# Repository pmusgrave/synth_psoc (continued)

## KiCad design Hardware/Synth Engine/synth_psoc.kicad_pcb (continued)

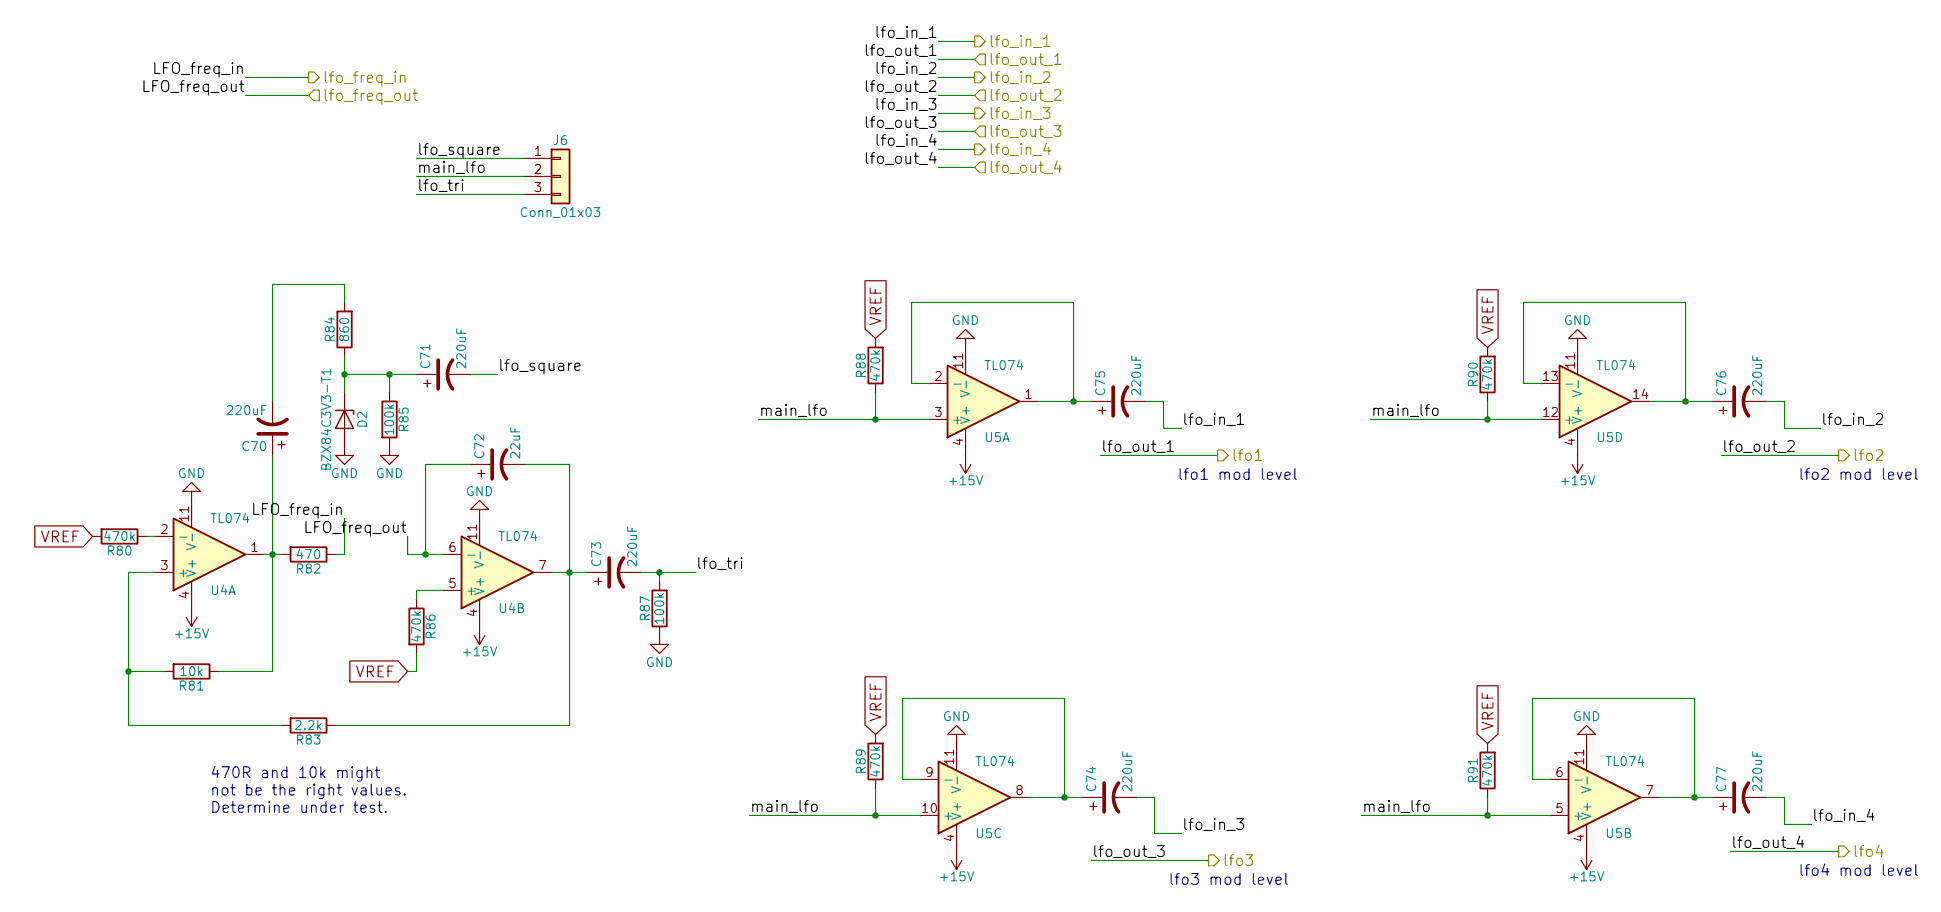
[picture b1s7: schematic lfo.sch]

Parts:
C70, C71, C73, C74, C75, C76, C77: 220uF; CP_Elec_8x10
C72: 22uF; CP_Elec_5x5.7
D2: BZX84C3V3-T1; SOT-23-3
J6: Conn_01x03; Pin_Header_Straight_1x03_Pitch2.54mm
R80, R86, R88, R89, R90, R91: 470k; 0805
R81: 10k; 0805
R82: 470; 0805
R83: 2.2k; 0805
R84: 860; 0805
R85, R87: 100k; 0805
U4, U5: TL074; SOIC-14_W3.9mm

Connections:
+15V: U4.4 (V+), U5.4 (V+); also elsewhere on the board
/LFO Modulation and Routing/lfo_square: C71.2, J6.1
/LFO Modulation and Routing/lfo_tri: C73.2, J6.3, R87.2
/LFO Modulation and Routing/main_lfo: J6.2, R88.1, R89.1, R90.1, R91.1, U5.3 (+), U5.5 (+), U5.10 (+), U5.12 (+)
/lfo_freq_in: R82.1; also elsewhere on the board
/lfo_freq_out: C72.1, U4.6 (-); also elsewhere on the board
/lfo_in_1: C75.2; also elsewhere on the board
/lfo_in_2: C76.2; also elsewhere on the board
/lfo_in_3: C74.2; also elsewhere on the board
/lfo_in_4: C77.2; also elsewhere on the board
GND: D2.2 (A), R85.2, R87.1, U4.11 (V-), U5.11 (V-); also elsewhere on the board
unnamed: C70.1, R81.1, R82.2, U4.1
unnamed: C70.2, R84.2
unnamed: C71.1, D2.1 (K), R84.1, R85.1
unnamed: C72.2, C73.1, R83.1, U4.7
unnamed: C74.1, U5.8, U5.9 (-)
unnamed: C75.1, U5.1, U5.2 (-)
unnamed: C76.1, U5.13 (-), U5.14
unnamed: C77.1, U5.6 (-), U5.7
unnamed: R80.1, U4.2 (-)
unnamed: R81.2, R83.2, U4.3 (+)
unnamed: R86.1, U4.5 (+)
VREF: R80.2, R86.2, R88.2, R89.2, R90.2, R91.2; also elsewhere on the board

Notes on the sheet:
470R and 10k might not be the right values. Determine under test.
lfo4 mod level
lfo2 mod level
lfo3 mod level
lfo1 mod level

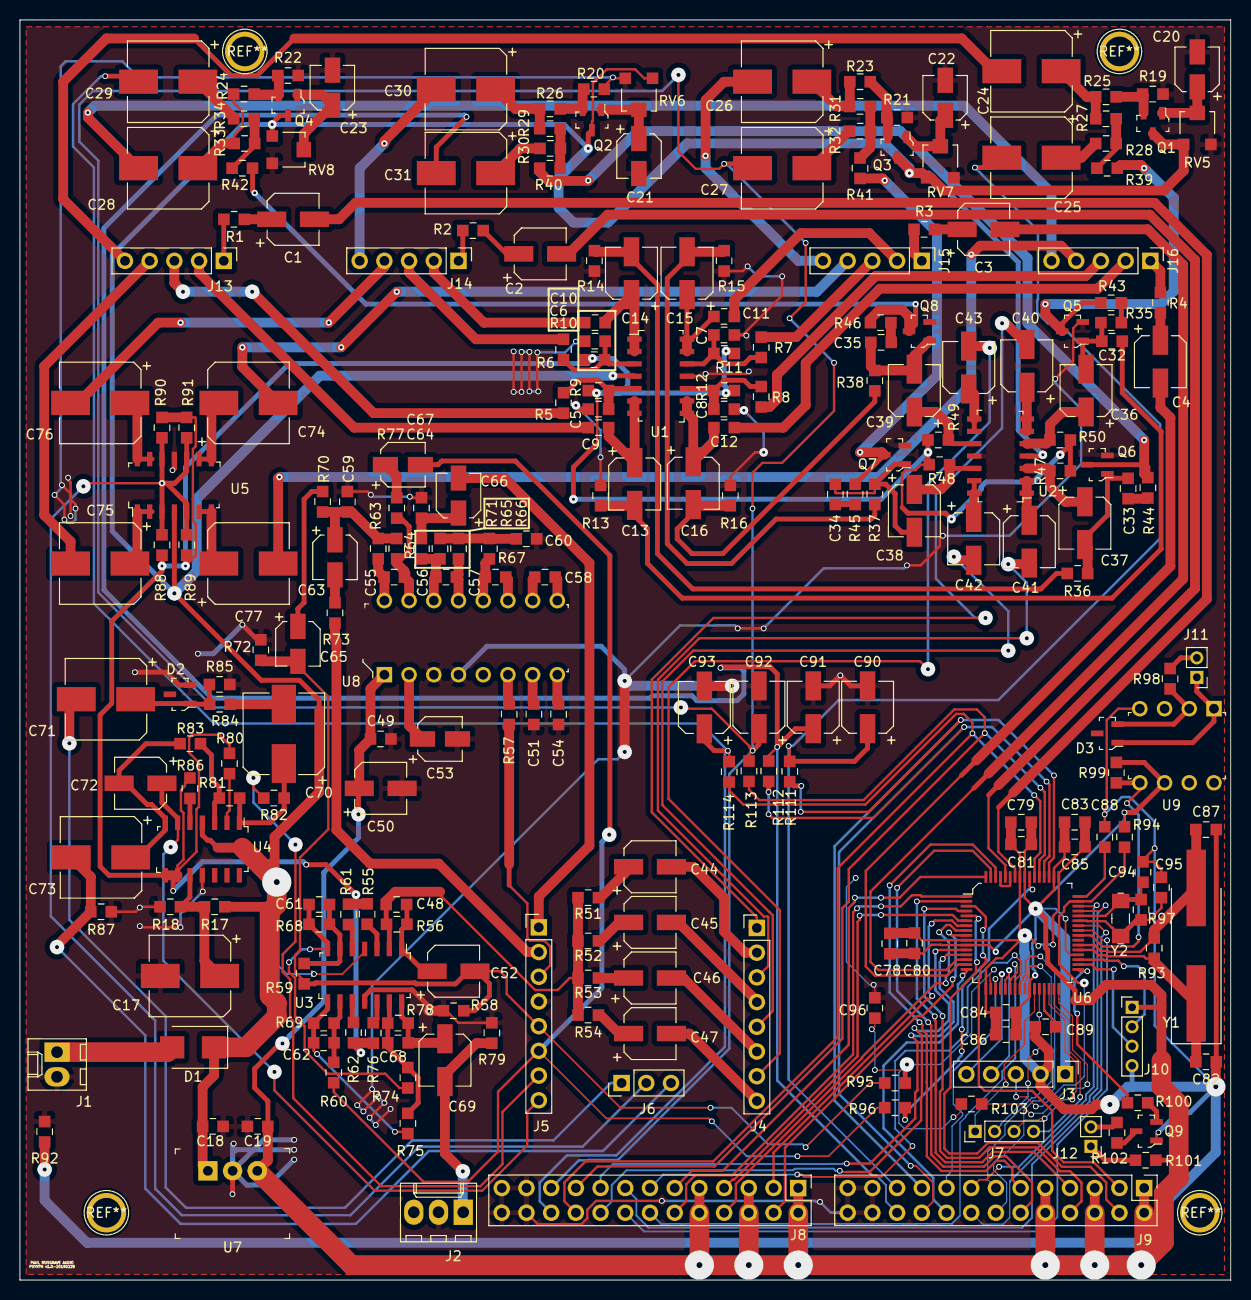
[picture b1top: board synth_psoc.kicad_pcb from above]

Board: 2 copper layers, 124.5 x 129.5 mm, 246 parts (0 on the bottom side), 211 nets.

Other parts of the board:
C96: 0.1uF; 0805
R103: 10k; 0805

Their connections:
/mcu_delay_in: C96.1, R103.1; also elsewhere on the board
GND: C96.2; also elsewhere on the board
unnamed 209: R103.2; also elsewhere on the board

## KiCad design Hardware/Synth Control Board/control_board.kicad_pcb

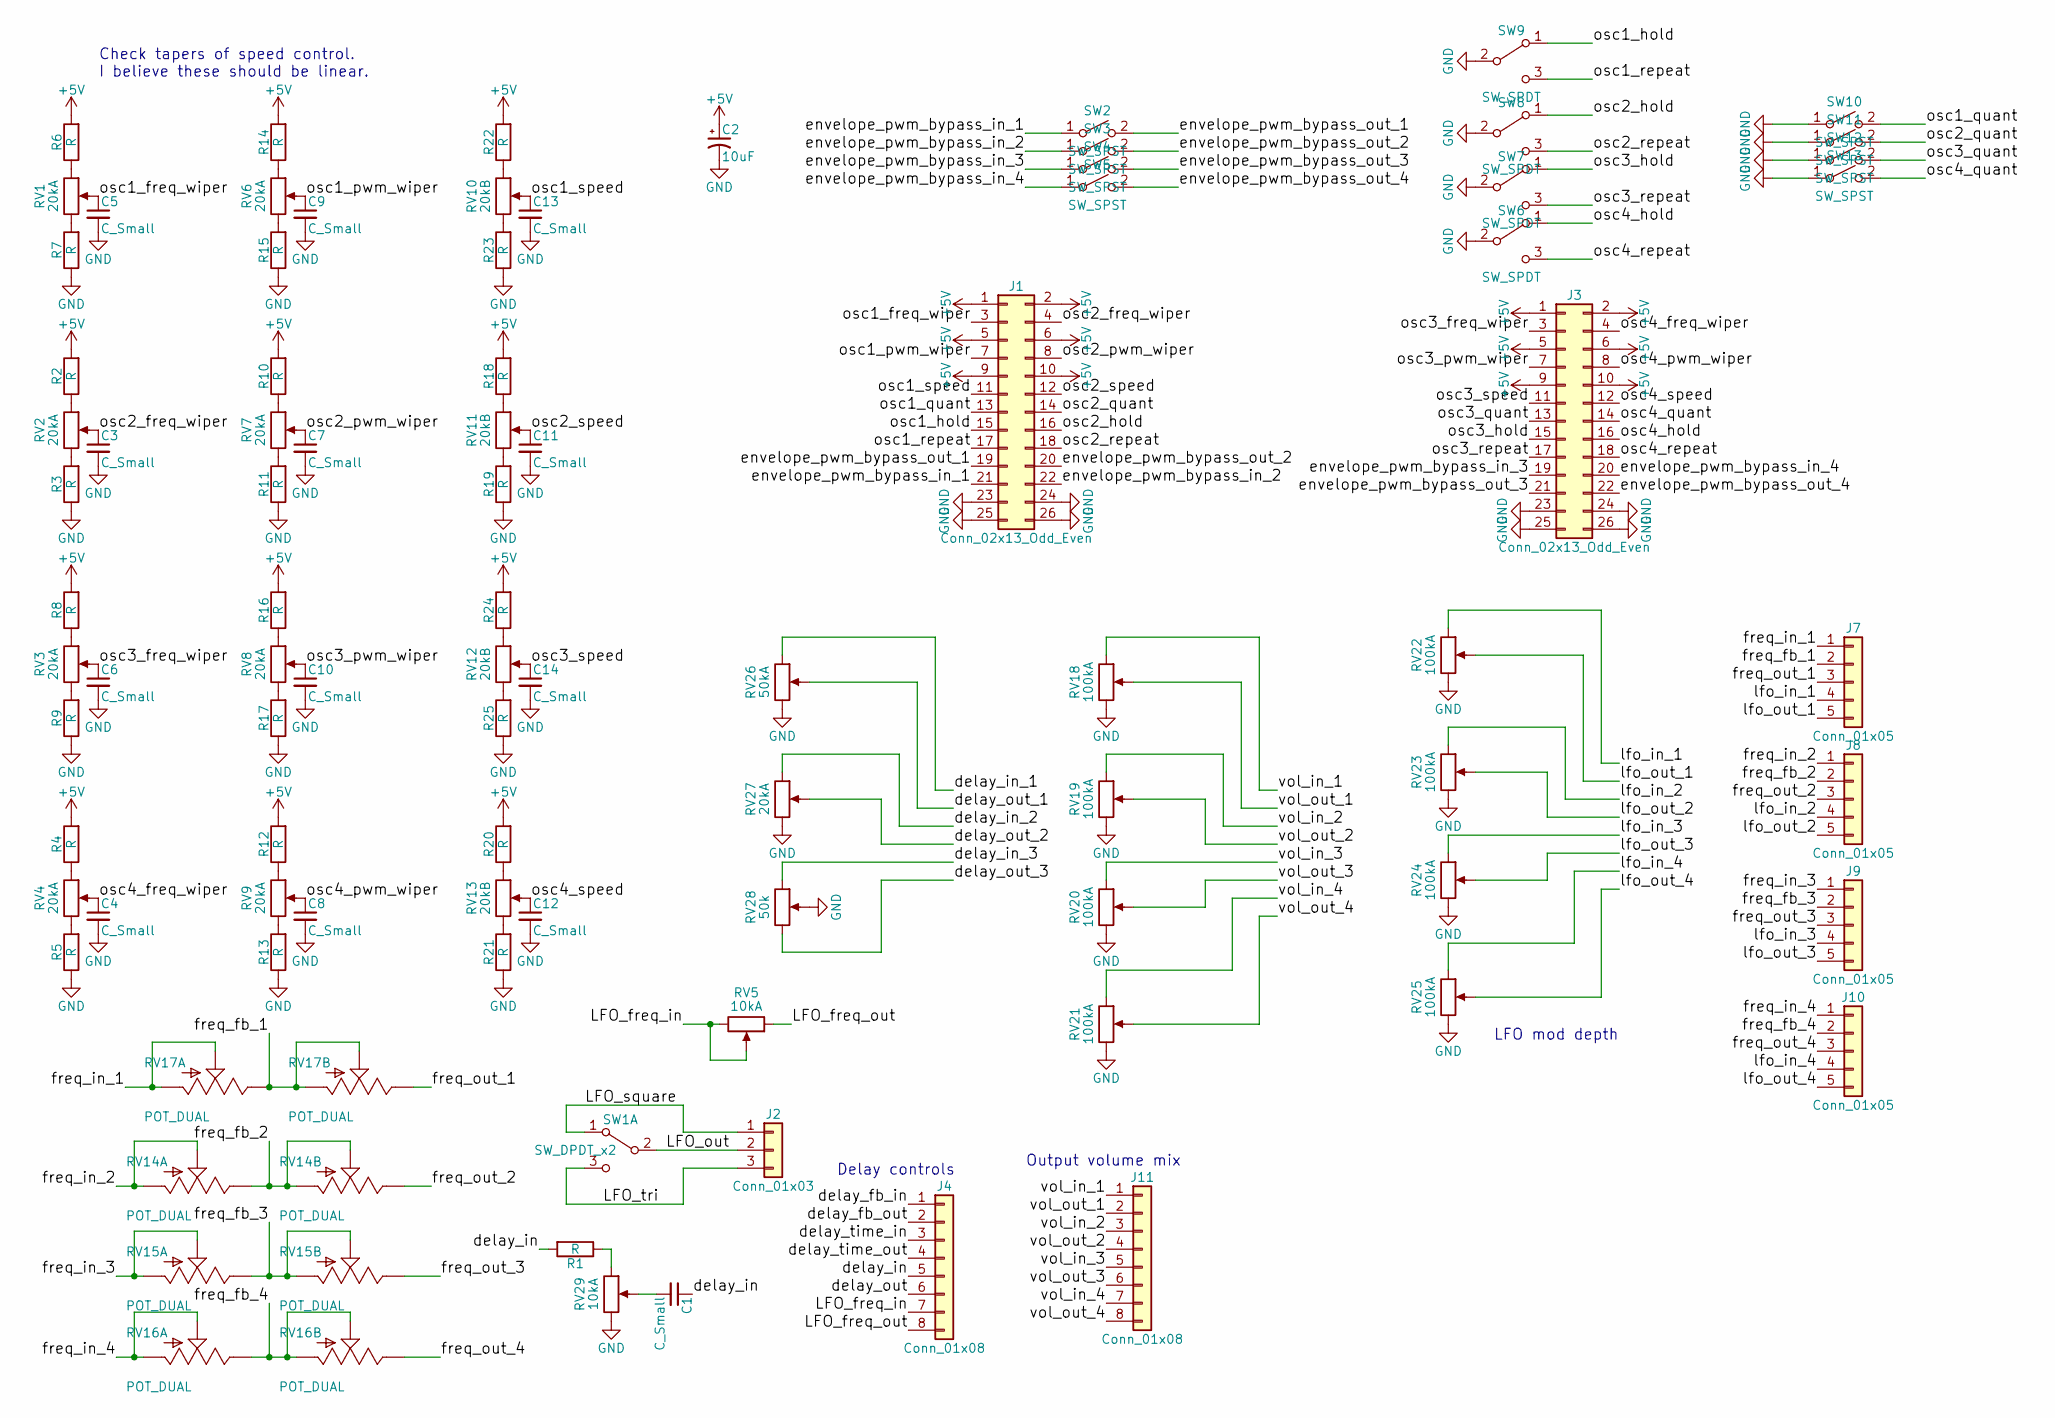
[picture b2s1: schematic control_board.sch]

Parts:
C1, C3, C4, C5, C6, C7, C8, C9, C10, C11, C12, C13, C14: C_Small; 0805
C2: 10uF; CP_Radial_D8.0mm_P5.00mm
J1, J3: Conn_02x13_Odd_Even; Pin_Header_Straight_2x13_Pitch2.54mm
J2: Conn_01x03; Pin_Header_Straight_1x03_Pitch2.54mm
J4, J11: Conn_01x08; Pin_Header_Straight_1x08_Pitch2.54mm
J7, J8, J9, J10: Conn_01x05; Pin_Header_Straight_1x05_Pitch2.54mm
R1, R2, R3, R4, R5, R6, R7, R8, R9, R10, R11, R12, R13, R14, R15, R16, R17, R18, R19, R20, R21, R22, R23, R24, R25: R; 0805
RV1, RV2, RV3, RV4, RV6, RV7, RV8, RV9, RV27: 20kA; Potentiometer_Bourns_PTV09A-1_Horizontal
RV5, RV29: 10kA; Potentiometer_Bourns_PTV09A-1_Horizontal
RV10, RV11, RV12, RV13: 20kB; Potentiometer_Bourns_PTV09A-1_Horizontal
RV14, RV15, RV16, RV17: POT_DUAL; POT_PANASONIC_DUAL_VERT_KIT
RV18, RV19, RV20, RV21, RV22, RV23, RV24, RV25: 100kA; Potentiometer_Bourns_PTV09A-1_Horizontal
RV26: 50kA; Potentiometer_Bourns_PTV09A-1_Horizontal
RV28: 50k; Potentiometer_Bourns_PTV09A-1_Horizontal
SW1: SW_DPDT_x2; switch_toggle_4.7mm_pitch
SW2, SW3, SW4, SW5, SW10, SW11, SW12, SW13: SW_SPST; switch_toggle_4.7mm_pitch
SW6, SW7, SW8, SW9: SW_SPDT; switch_toggle_4.7mm_pitch

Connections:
+5V: C2.1, J1.1, J1.2, J1.5, J1.6, J1.9, J1.10, J3.1, J3.2, J3.5, J3.6, J3.9, J3.10, R2.2, R4.2, R6.2, R8.2, R10.2, R12.2, R14.2, R16.2, R18.2, R20.2, R22.2, R24.2
/LFO_freq_in: J4.7, RV5.2, RV5.3
/LFO_freq_out: J4.8, RV5.1
/LFO_out: J2.2, SW1.2 (B)
/LFO_square: J2.1, SW1.1 (A)
/LFO_tri: J2.3, SW1.3 (C)
/delay_fb_in: J4.1
/delay_fb_out: J4.2
/delay_in: C1.1, J4.5, R1.2
/delay_in_1: RV26.1
/delay_in_2: RV27.1
/delay_in_3: RV28.1
/delay_out: J4.6
/delay_out_1: RV26.2
/delay_out_2: RV27.2
/delay_out_3: RV28.3
/delay_time_in: J4.3
/delay_time_out: J4.4
/envelope_pwm_bypass_in_1: J1.21, SW2.1 (A)
/envelope_pwm_bypass_in_2: J1.22, SW3.1 (A)
/envelope_pwm_bypass_in_3: J3.19, SW4.1 (A)
/envelope_pwm_bypass_in_4: J3.20, SW5.1 (A)
/envelope_pwm_bypass_out_1: J1.19, SW2.2 (B)
/envelope_pwm_bypass_out_2: J1.20, SW3.2 (B)
/envelope_pwm_bypass_out_3: J3.21, SW4.2 (B)
/envelope_pwm_bypass_out_4: J3.22, SW5.2 (B)
/freq_fb_1: J7.2, RV17.A1 (E), RV17.B2 (S), RV17.B3 (A)
/freq_fb_2: J8.2, RV14.A1 (E), RV14.B2 (S), RV14.B3 (A)
/freq_fb_3: J9.2, RV15.A1 (E), RV15.B2 (S), RV15.B3 (A)
/freq_fb_4: J10.2, RV16.A1 (E), RV16.B2 (S), RV16.B3 (A)
/freq_in_1: J7.1, RV17.A2 (S), RV17.A3 (A)
/freq_in_2: J8.1, RV14.A2 (S), RV14.A3 (A)
/freq_in_3: J9.1, RV15.A2 (S), RV15.A3 (A)
/freq_in_4: J10.1, RV16.A2 (S), RV16.A3 (A)
/freq_out_1: J7.3, RV17.B1 (E)
/freq_out_2: J8.3, RV14.B1 (E)
/freq_out_3: J9.3, RV15.B1 (E)
/freq_out_4: J10.3, RV16.B1 (E)
/lfo_in_1: J7.4, RV22.1
/lfo_in_2: J8.4, RV23.1
/lfo_in_3: J9.4, RV24.1
/lfo_in_4: J10.4, RV25.1
/lfo_out_1: J7.5, RV22.2
/lfo_out_2: J8.5, RV23.2
/lfo_out_3: J9.5, RV24.2
/lfo_out_4: J10.5, RV25.2
/osc1_freq_wiper: C5.1, J1.3, RV1.2
/osc1_hold: J1.15, SW9.1 (A)
/osc1_pwm_wiper: C9.1, J1.7, RV6.2
/osc1_quant: J1.13, SW10.2 (B)
/osc1_repeat: J1.17, SW9.3 (C)
/osc1_speed: C13.1, J1.11, RV10.2
/osc2_freq_wiper: C3.1, J1.4, RV2.2
/osc2_hold: J1.16, SW8.1 (A)
/osc2_pwm_wiper: C7.1, J1.8, RV7.2
/osc2_quant: J1.14, SW11.2 (B)
/osc2_repeat: J1.18, SW8.3 (C)
/osc2_speed: C11.1, J1.12, RV11.2
/osc3_freq_wiper: C6.1, J3.3, RV3.2
/osc3_hold: J3.15, SW7.1 (A)
/osc3_pwm_wiper: C10.1, J3.7, RV8.2
/osc3_quant: J3.13, SW12.2 (B)
/osc3_repeat: J3.17, SW7.3 (C)
/osc3_speed: C14.1, J3.11, RV12.2
/osc4_freq_wiper: C4.1, J3.4, RV4.2
/osc4_hold: J3.16, SW6.1 (A)
/osc4_pwm_wiper: C8.1, J3.8, RV9.2
/osc4_quant: J3.14, SW13.2 (B)
/osc4_repeat: J3.18, SW6.3 (C)
/osc4_speed: C12.1, J3.12, RV13.2
/vol_in_1: J11.1, RV18.1
/vol_in_2: J11.3, RV19.1
/vol_in_3: J11.5, RV20.1
/vol_in_4: J11.7, RV21.1
/vol_out_1: J11.2, RV18.2
/vol_out_2: J11.4, RV19.2
/vol_out_3: J11.6, RV20.2
/vol_out_4: J11.8, RV21.2
GND: C2.2, C3.2, C4.2, C5.2, C6.2, C7.2, C8.2, C9.2, C10.2, C11.2, C12.2, C13.2, C14.2, J1.23, J1.24, J1.25, J1.26, J3.23, J3.24, J3.25, J3.26, R3.1, R5.1, R7.1, R9.1, R11.1, R13.1, R15.1, R17.1, R19.1, R21.1, R23.1, R25.1, RV18.3, RV19.3, RV20.3, RV21.3, RV22.3, RV23.3, RV24.3, RV25.3, RV26.3, RV27.3, RV28.2, RV29.3, SW6.2 (B), SW7.2 (B), SW8.2 (B), SW9.2 (B), SW10.1 (A), SW11.1 (A), SW12.1 (A), SW13.1 (A)
unnamed: C1.2, RV29.2
unnamed: R1.1, RV29.1
unnamed: R2.1, RV2.1
unnamed: R3.2, RV2.3
unnamed: R4.1, RV4.1
unnamed: R5.2, RV4.3
unnamed: R6.1, RV1.1
unnamed: R7.2, RV1.3
unnamed: R8.1, RV3.1
unnamed: R9.2, RV3.3
unnamed: R10.1, RV7.1
unnamed: R11.2, RV7.3
unnamed: R12.1, RV9.1
unnamed: R13.2, RV9.3
unnamed: R14.1, RV6.1
unnamed: R15.2, RV6.3
unnamed: R16.1, RV8.1
unnamed: R17.2, RV8.3
unnamed: R18.1, RV11.1
unnamed: R19.2, RV11.3
unnamed: R20.1, RV13.1
unnamed: R21.2, RV13.3
unnamed: R22.1, RV10.1
unnamed: R23.2, RV10.3
unnamed: R24.1, RV12.1
unnamed: R25.2, RV12.3

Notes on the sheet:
Check tapers of speed control. I believe these should be linear.
Output volume mix
LFO mod depth
Delay controls

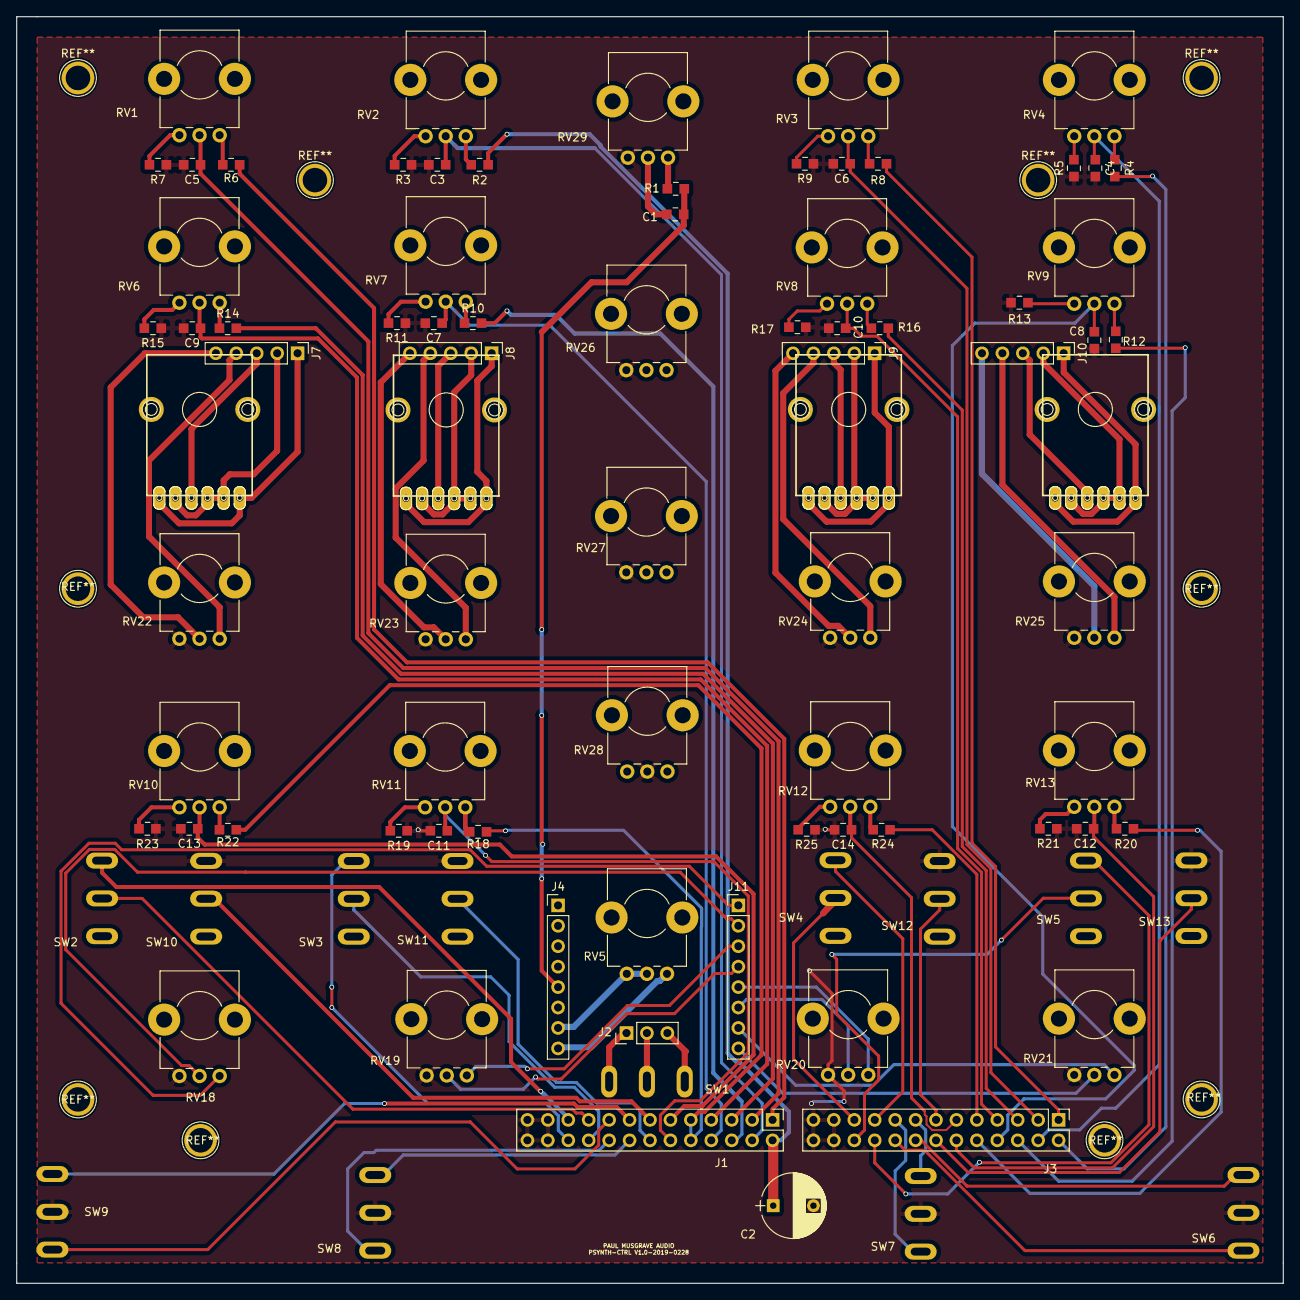
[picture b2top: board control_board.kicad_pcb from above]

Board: 2 copper layers, 157.5 x 157.5 mm, 90 parts (0 on the bottom side), 94 nets.

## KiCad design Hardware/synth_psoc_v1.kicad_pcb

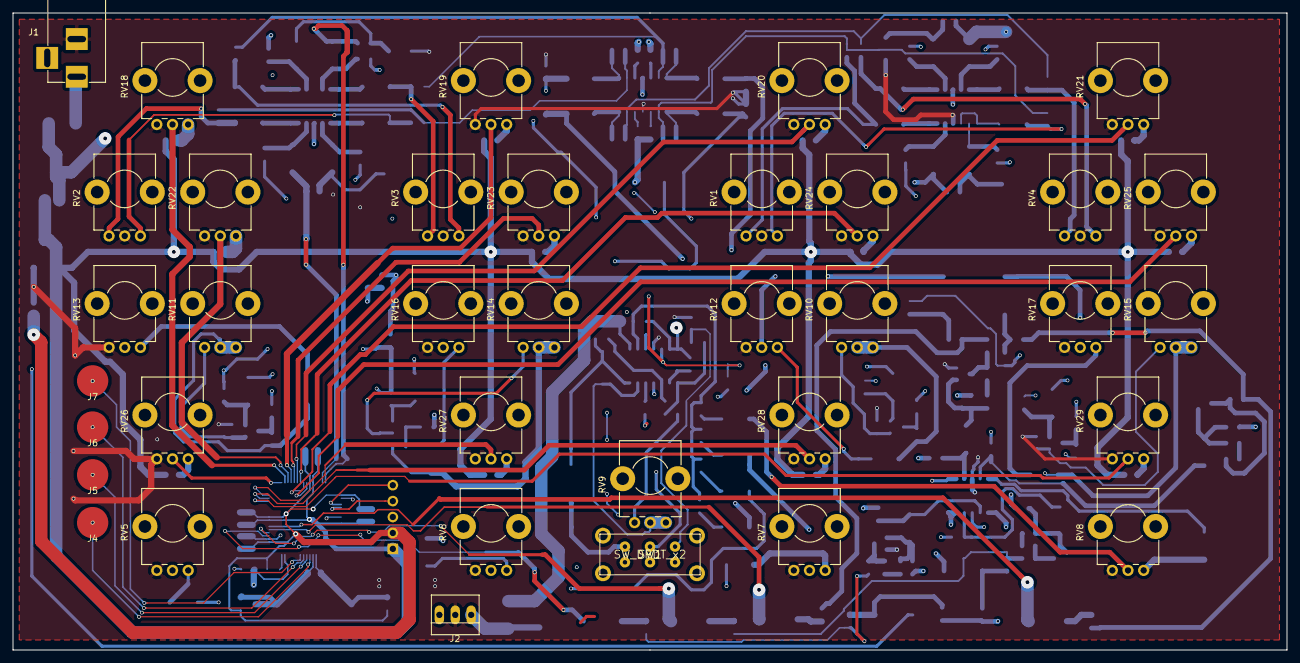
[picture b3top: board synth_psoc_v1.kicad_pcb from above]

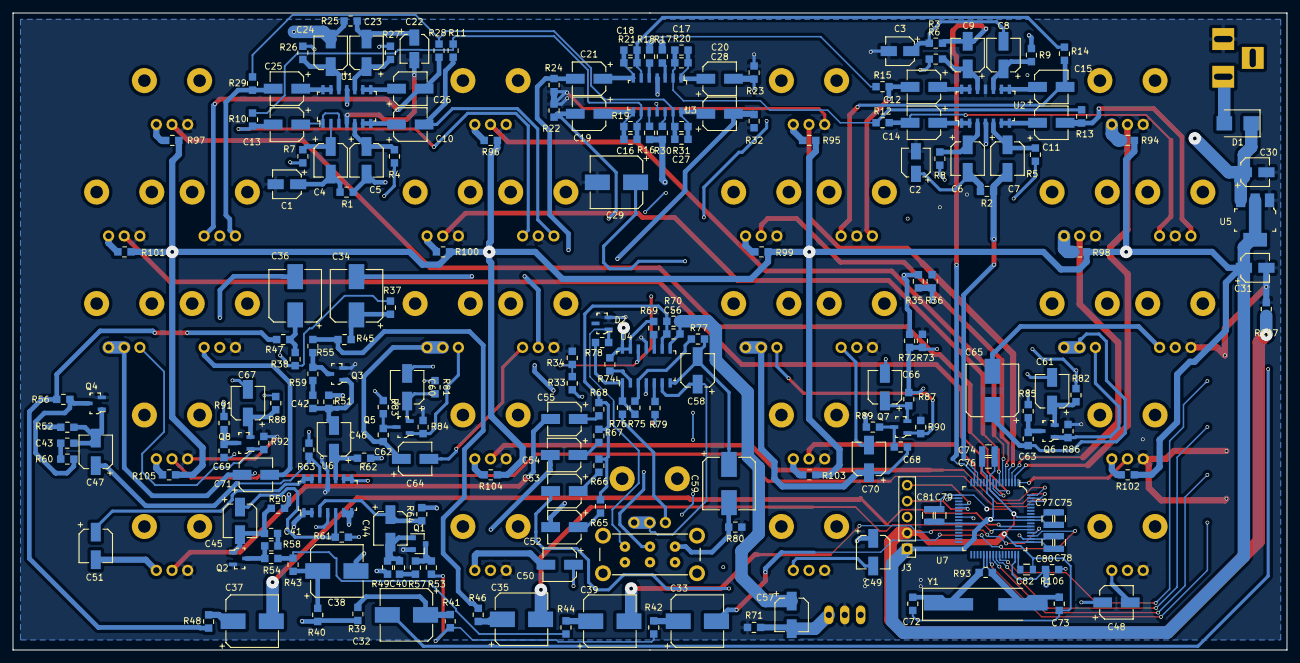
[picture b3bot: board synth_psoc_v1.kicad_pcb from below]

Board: 4 copper layers, 203.2 x 101.6 mm, 244 parts (208 on the bottom side), 177 nets.

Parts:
C1, C2, C3, C22, C30: 1uF; CP_Elec_4x4.5
C4, C5, C6, C7, C8, C9, C10, C11, C12, C13, C14, C15, C19, C20, C21, C23, C24, C25, C26, C28, C44, C45, C46, C47, C48, C49, C50, C51, C52, C53, C54, C55, C57, C58, C60, C61, C64, C66, C67, C70, C71: 22uF; CP_Elec_5x5.7
C16, C17, C18, C27: 100p; 0805
C29, C59, C65: 220uF; CP_Elec_8x10
C31: 4.7uF; CP_Elec_4x5.7
C32, C33, C34, C35, C36, C37, C38, C39: 220u; CP_Elec_8x10
C40, C41, C42, C43: 1nF; 0805
C56: 100pF; 0805
C62, C63, C68, C69: 33nF; 0805
C72, C73: 22pF; 0805
C74, C75, C78, C81, C82: 1uF; C_0805
C76, C77, C79, C80: 0.1uF; C_0805
D1: D_Schottky; D_SMB
D2: BZX84C3V3-T1; SOT-23-3
J1: Barrel_Jack; BARREL_JACK
J2: Audio-Jack-2_Switch; PINHEAD1-3
J3: SWD_programming; Pin_Header_Straight_1x05_Pitch2.54mm
J4: Capsense_0; Capsense_button
J5: Capsense_1; Capsense_button
J6: Capsense_2; Capsense_button
J7: Capsense_3; Capsense_button
Q1: MMBFJ177; SOT-23
Q2, Q3, Q4: MMBFJ177; SOT-23-3
Q5, Q6, Q7, Q8: 2N3904; SOT-23-3
R1, R2, R3, R25: 1k; 0805
R4, R5, R6, R7, R8, R9, R16, R17, R18, R26, R27, R30, R37, R38, R39, R40, R61, R62, R63, R64, R69, R74, R79, R81, R82, R87, R88: 470k; 0805
R10, R11, R12, R13, R14, R15, R19, R20, R21, R28, R29, R31, R65, R66, R67, R68, R70, R71, R72, R73, R75, R83, R84, R85, R86, R89, R90, R91, R92: 10k; 0805
R22, R23, R24, R32, R33, R34, R80: 100k; 0805
R35, R36, R49, R50, R51, R52: 22k; 0805
R41, R43, R45, R47, R53, R54, R55, R56, R57, R58, R59, R60, R93: 1MEG; 0805
R42, R44, R46, R48: 500k; 0805
R76: 470; 0805
R77: 2.2k; 0805
R78: 860; 0805
R94, R95, R96, R97, R98, R99, R100, R101, R102, R103, R104, R105, R106, R107: R; 0805
RV1, RV2, RV3, RV4: 100k-S; Potentiometer_Bourns_PTV09A-1_Horizontal
RV5, RV6, RV7, RV8: 100k; Potentiometer_Bourns_PTV09A-1_Horizontal
RV9, RV12, RV13, RV16, RV17: 10kA; Potentiometer_Bourns_PTV09A-1_Horizontal
RV10, RV11, RV14, RV15: 10kB; Potentiometer_Bourns_PTV09A-1_Horizontal
RV18, RV19, RV20, RV21, RV22, RV23, RV24, RV25: 20kA; Potentiometer_Bourns_PTV09A-1_Horizontal
RV26, RV27, RV28, RV29: 20kB; Potentiometer_Bourns_PTV09A-1_Horizontal
SW1: SW_DPDT_x2; SWITCHE-DPDT
U1, U2, U3, U4, U6: TL074; SOIC-14_W3.9mm
U5: LD1117S33CTR; SOT-223
U7: CY8C4246AZI-L445; LQFP-64_10x10mm
Y1: Crystal; Crystal_SMD_HC49-SD_HandSoldering

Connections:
+3V3: C31.1, C74.1, C75.1, C76.1, C77.1, C78.1, C79.1, C80.1, C81.1, J3.1, R94.1, R95.1, R96.1, R97.1, R98.1, R99.1, R100.1, R101.1, R102.1, R103.1, R104.1, R105.1, R106.1, U5.2, U5.4, U7.11, U7.26, U7.50, U7.56
+15V: C30.1, D1.1, R33.1, R35.2, R72.1, R83.1, R85.1, R89.1, R91.1, U1.11, U2.4, U3.4, U4.4, U5.3, U6.4
/Envelope/env_out_1: C52.2, RV5.2
/Envelope/env_out_2: C53.2, RV6.2
/Envelope/env_out_3: C54.2, RV7.2
/Envelope/env_out_4: C55.2, RV8.2
/Envelope/lfo1: C32.2, RV13.2
/Envelope/lfo2: C38.2, RV16.2
/Envelope/lfo3: C34.2, RV12.2
/Envelope/lfo4: C36.2, RV17.2
/Envelope/lfo_bias: R35.1, R36.2, R37.1, R38.1, R39.1, R40.1
/Filters/filter_out_1: C20.2, R23.1, R49.2
/Filters/filter_out_2: C21.2, R24.1, R50.2
/Filters/filter_out_3: C19.2, R22.1, R51.2
/Filters/filter_out_4: C28.2, R32.1, R52.2
/Filters/osc1: C7.2, R2.2, U7.14
/Filters/osc2: C9.2, R3.2, U7.15
/Filters/osc3: C5.2, R1.2, U7.18
/Filters/osc4: C24.2, R25.2, U7.24
/LFO Modulation and Routing/bias: R72.2, R73.1, R81.1, R82.1, R87.1, R88.1
/LFO Modulation and Routing/lfo_square: D2.1, R78.1, SW1.3
/LFO Modulation and Routing/lfo_tri: C59.2, R80.2, SW1.1
/LFO Modulation and Routing/main_lfo: C60.2, C61.2, C66.2, C67.2, SW1.2
/Microcontroller/SCLK: J3.4, U7.21
/Microcontroller/SDAT: J3.5, U7.20
/Microcontroller/XRES: J3.3, R106.2, U7.47
/Microcontroller/envelope_pwm_1: C33.2, U7.51
/Microcontroller/envelope_pwm_2: C39.2, U7.52
/Microcontroller/envelope_pwm_3: C35.2, U7.53
/Microcontroller/envelope_pwm_4: C37.2, U7.54
/Microcontroller/osc1_freq_wiper: RV18.2, U7.2
/Microcontroller/osc1_pwm_wiper: RV22.2, U7.3
/Microcontroller/osc1_speed: RV26.2, U7.1
/Microcontroller/osc2_freq_wiper: RV19.2, U7.4
/Microcontroller/osc2_pwm_wiper: RV23.2, U7.5
/Microcontroller/osc2_speed: RV27.2, U7.64
/Microcontroller/osc3_freq_wiper: RV20.2, U7.6
/Microcontroller/osc3_pwm_wiper: RV24.2, U7.7
/Microcontroller/osc3_speed: RV28.2, U7.63
/Microcontroller/osc4_freq_wiper: RV21.2, U7.8
/Microcontroller/osc4_pwm_wiper: RV25.2, U7.9
/Microcontroller/osc4_speed: RV29.2, U7.62
GND: C1.2, C2.2, C3.2, C22.2, C29.2, C30.2, C31.2, D2.2, J1.2, J2.2, Q1.2, Q2.2, Q3.2, Q4.2, R22.2, R23.2, R24.2, R32.2, R34.2, R36.1, R71.1, R73.2, R80.1, R84.2, R86.2, R90.2, R92.2, R107.1, RV1.2, RV2.2, RV3.2, RV4.2, RV5.3, RV6.3, RV7.3, RV8.3, RV12.3, RV13.3, RV16.3, RV17.3, RV18.3, RV19.3, RV20.3, RV21.3, RV22.3, RV23.3, RV24.3, RV25.3, RV26.3, RV27.3, RV28.3, RV29.3, U1.4, U2.11, U3.11, U4.11, U5.1, U6.11
GNDD: C72.2, C73.2, C74.2, C75.2, C76.2, C77.2, C78.2, C79.2, C80.2, C81.2, C82.2, J3.2, R107.2, U7.10, U7.17, U7.49, U7.57
unnamed: C1.1, C4.2, R1.1
unnamed: C2.1, C6.2, R2.1
unnamed: C3.1, C8.2, R3.1
unnamed: C4.1, R7.2, U1.2
unnamed: C5.1, R4.2, U1.5
unnamed: C6.1, R8.2, U2.3
unnamed: C7.1, R5.2, U2.5
unnamed: C8.1, R9.2, U2.10
unnamed: C9.1, R6.2, U2.12
unnamed: C10.1, U1.6, U1.7
unnamed: C10.2, R11.2, RV1.3
unnamed: C11.1, U2.6, U2.7
unnamed: C11.2, R13.2, RV2.3
unnamed: C12.1, U2.13, U2.14
unnamed: C12.2, R15.2, RV3.3
unnamed: C13.1, U1.1, U1.3
unnamed: C13.2, R10.2, RV1.1
unnamed: C14.1, U2.1, U2.2
unnamed: C14.2, R12.2, RV2.1
unnamed: C15.1, U2.8, U2.9
unnamed: C15.2, R14.2, RV3.1
unnamed: C16.1, C19.1, R19.1, U3.8
unnamed: C16.2, R10.1, R11.1, R19.2, U3.9
unnamed: C17.1, C20.1, R20.1, U3.1
unnamed: C17.2, R12.1, R13.1, R20.2, U3.2
unnamed: C18.1, C21.1, R21.1, U3.7
unnamed: C18.2, R14.1, R15.1, R21.2, U3.6
unnamed: C22.1, C23.2, R25.1
unnamed: C23.1, R27.2, U1.10
unnamed: C24.1, R26.2, U1.12
unnamed: C25.1, U1.13, U1.14
unnamed: C25.2, R29.2, RV4.3
unnamed: C26.1, U1.8, U1.9
unnamed: C26.2, R28.2, RV4.1
unnamed: C27.1, C28.1, R31.1, U3.14
unnamed: C27.2, R28.1, R29.1, R31.2, U3.13
unnamed: C29.1, R33.2, R34.1, U4.12
unnamed: C32.1, R39.2, R41.2
unnamed: C33.1, R42.2
unnamed: C34.1, R37.2, R45.2
unnamed: C35.1, R46.2
unnamed: C36.1, R38.2, R47.2
unnamed: C37.1, R48.2
unnamed: C38.1, R40.2, R43.2
unnamed: C39.1, R44.2
unnamed: C40.1, R57.2
unnamed: C40.2, C44.2, Q1.1, R49.1
unnamed: C41.1, R58.2
unnamed: C41.2, C45.2, Q2.1, R50.1
unnamed: C42.1, R59.2
unnamed: C42.2, C46.2, Q3.1, R51.1
unnamed: C43.1, R60.2
unnamed: C43.2, C47.2, Q4.1, R52.1
unnamed: C44.1, R64.1, U6.3
unnamed: C45.1, R61.1, U6.5
unnamed: C46.1, R62.1, U6.10
unnamed: C47.1, R63.1, U6.12
unnamed: C48.1, U6.1, U6.2
unnamed: C48.2, RV5.1
unnamed: C49.1, U6.6, U6.7
unnamed: C49.2, RV6.1
unnamed: C50.1, U6.8, U6.9
unnamed: C50.2, RV7.1
unnamed: C51.1, U6.13, U6.14
unnamed: C51.2, RV8.1
unnamed: C52.1, R65.2
unnamed: C53.1, R66.2
unnamed: C54.1, R67.2
unnamed: C55.1, R68.2
unnamed: C56.1, C57.1, R70.1, U4.8
unnamed: C56.2, R65.1, R66.1, R67.1, R68.1, R70.2, U4.9
unnamed: C57.2, J2.1, R71.2
unnamed: C58.1, RV9.1, RV9.2, U4.6
unnamed: C58.2, C59.1, R77.1, U4.7
unnamed: C60.1, Q5.2, R81.2
unnamed: C61.1, Q6.2, R82.2
unnamed: C62.1, Q5.3, R83.2
unnamed: C62.2, C64.1, RV10.1, RV10.2
unnamed: C63.1, Q6.3, R85.2
unnamed: C63.2, C65.1, RV11.1, RV11.2
unnamed: C64.2, RV12.1
unnamed: C65.2, RV13.1
unnamed: C66.1, Q7.2, R87.2
unnamed: C67.1, Q8.2, R88.2
unnamed: C68.1, Q7.3, R89.2
unnamed: C68.2, C70.1, RV14.1, RV14.2
unnamed: C69.1, Q8.3, R91.2
unnamed: C69.2, C71.1, RV15.1, RV15.2
unnamed: C70.2, RV16.1
unnamed: C71.2, RV17.1
unnamed: C72.1, R93.2, U7.37, Y1.1
unnamed: C73.1, R93.1, U7.38, Y1.2
unnamed: C82.1, U7.48
unnamed: D1.2, J1.1
unnamed: J4.1, U7.39
unnamed: J5.1, U7.40
unnamed: J6.1, U7.41
unnamed: J7.1, U7.42
unnamed: Q1.3, R53.1, R57.1
unnamed: Q2.3, R54.1, R58.1
unnamed: Q3.3, R55.1, R59.1
unnamed: Q4.3, R56.1, R60.1
unnamed: Q5.1, R84.1, RV10.3
unnamed: Q6.1, R86.1, RV11.3
unnamed: Q7.1, R90.1, RV14.3
unnamed: Q8.1, R92.1, RV15.3
unnamed: R16.1, U3.10
unnamed: R17.1, U3.3
unnamed: R18.1, U3.5
unnamed: R30.1, U3.12
unnamed: R41.1, R42.1, R53.2
unnamed: R43.1, R44.1, R54.2
unnamed: R45.1, R46.1, R55.2
unnamed: R47.1, R48.1, R56.2
unnamed: R69.1, U4.10
unnamed: R74.1, U4.2
unnamed: R75.1, R76.2, R78.2, U4.1
unnamed: R75.2, R77.2, U4.3
unnamed: R76.1, RV9.3
unnamed: R79.1, U4.5
unnamed: R94.2, RV18.1
unnamed: R95.2, RV19.1
unnamed: R96.2, RV20.1
unnamed: R97.2, RV21.1
unnamed: R98.2, RV22.1
unnamed: R99.2, RV23.1
unnamed: R100.2, RV24.1
unnamed: R101.2, RV25.1
unnamed: R102.2, RV26.1
unnamed: R103.2, RV27.1
unnamed: R104.2, RV28.1
unnamed: R105.2, RV29.1
VREF: R4.1, R5.1, R6.1, R7.1, R8.1, R9.1, R16.2, R17.2, R18.2, R26.1, R27.1, R30.2, R61.2, R62.2, R63.2, R64.2, R69.2, R74.2, R79.2, U4.13, U4.14

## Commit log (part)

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2018-01-18 move from PSoC training repo
2018-07-17 change of project definition migrating from just a DCO to a full synth renamed project from DCO to synth_psoc started to add envelope generator to project also added some notes for later regarding pu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
2018-07-17 begin code for reading ADSR pot values this is unfinished and untested
2018-07-17 hardware config already changed due to PSOC routing add init code for envelope generator potentiometers
2018-07-17 add envelope trigger switch debounced interrupt connected to switch input currently toggling an LED as a test
2018-07-18 push button to trigger the start of an envelope envelope currently fades an LED up to a value set by the attack pot
2018-07-18 potentiometer sets timer period, which is the correct way to change the slope fixes bug from previous commit
2018-07-24 ADSR switches between all four modes pushbutton to trigger, stays in sustain mode until another button press green LED indicates sustain mode is active
2018-07-24 starting to prototype LFO with red LED freq currently set by same knob as square wave oscillator
2019-01-03 move square wave output to match breadboard
2019-01-03 move all ISRs into separate files for readability
2019-01-03 oscillator known good state frequency and PWM knobs are both working square wave output is what it should be
2019-01-03 move oscillator code to separate header and source files for readability
2019-01-03 fixes ADSR mode switching. press button to trigger ADSR, ENABLE_TIMER will switch modes on compare match. Currently, sustain mode can only be exited by a second button press. Time values are correct,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
2019-01-04 fixes ADSR ramp. still has some bugs: speed is still too low, probably need to change to log pots, some pot values create a glitch where the timer doesn't overflow and it never changes modes, it jump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
2019-01-04 move envelope output to inverted pwm driver for driving the gate of a P-channel FET
2019-01-05 moved code into Firmware directory and added Hardware directory for electronics documentation
2019-01-05 clean up after moving code to new directory
2019-01-08 modify entire firmware to fit on a CY8CKIT-049. Original dev board not functioning, working on this one until replacement board arrives
2019-01-08 update readme to reflect change in project scope
2019-01-08 add SPICE simulation files to project directory
2019-01-09 initial schematic commit. create hierarchical sheets for microcontroller and filters
2019-01-09 add sheets for the remaining functionality. This should hopefully be all sheets, but might add more if necessary.
2019-01-09 add basic version of VCA for one channel
2019-01-09 add bill of materials spreadsheet and begin to populate with values
2019-01-10 add mcu, crystal, and programming header to schematic
2019-01-10 complete wiring of top level schematic hierarchical pages
2019-01-10 complete filters for all 4 oscs
2019-01-10 add power jack, 3.3V regulator, VREF divider
2019-01-10 change corner frequency of DC blocking caps everywhere they are in use. Updated some simulation files to test filter circuits.
2019-01-11 add analog LFO to schematic
2019-01-11 begin to add taper to potentiometers. I think they're all right, but some tapers may change under test.
2019-01-11 add LFO waveshape selector switch
2019-01-12 4 oscillators are working at once
2019-01-12 fix dropout issue with multiple osc voices.
2019-01-13 add freq and pulse width pots for 8 oscillators. Still needs to be tested on dev board and built, but I wanted to go ahead and add them to the schematic as an option.
2019-01-14 add 1Meg + 1nF cap to JFET base to improve biasing linearity.
2019-01-14 start to test CapSense buttons. This should probably be done on a different branch, though, so I'm not going to do very much more on this branch.
2019-01-14 Capsense button enables all oscillators. testing WIP.
2019-01-14 mix LFO and Envelope drive signals instead of switching them, and add overall volume mix control to each channel.
2019-01-14 update pinout with latest changes for production IC
2019-01-14 measure positions of potentiometers and tentative board edge definition.
2019-01-15 fix annotation and footprints for multi-part op amps.
2019-01-15 loosely organize components into groups based on their functionality
2019-01-16 MCU bypass capacitor routing complete
2019-01-16 gettin' there. WIP
2019-01-17 complete initial PCB layout. CapSense buttons still not done, but everything else should be there. I had to increase to a 4-layer board to keep the dimensions 8"x4".
2019-01-17 as built v1 boards, 2019-01-16 with gerber outputs
2019-01-17 some basic planning on price point, sales, and profitability.
2019-01-17 add envelope speed ADC inputs to firmware
2019-01-17 scan all 4 capsense buttons and enable oscillators independently. Also did some refactoring of the oscillator module and main.
2019-01-18 move capsense button conditionals into a function. Arguments are the capsense widget to be checked, a function pointer to the start and stop functions for the corresponding oscillator. This could pro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
2019-01-18 change osc speed controls to digital inputs. These will be switches on the prototype, because I don't have enough timers for 4 envelope PWMs, but made them that way on the board.
2019-01-18 fix missing connection of envelope outputs on MCU schematic page
2019-01-30 fix some bias voltage issues in the LFO schematic. Also begin working on envelope firmware, but this is in progress.
2019-01-30 saved in wrong folder
2019-01-30 define notes as preprocessor macros. This is going to change, but I don't want to have to redo any of it in case I need it.
2019-01-30 add documentation for music note frequencies
2019-01-30 add LPF to envelope PWM signals, and some test code for ramping up the PWM out of the micro.
2019-01-31 temporarily use PW pot for envelope attack/release time. Multiplying adc reading by 0.002 as an envelope increment works well experimentally.
2019-01-31 add Cmod cap to microcontroller for capsense operation.
2019-01-31 simulate correct corner frequency for new LPF circuit.
2019-01-31 change 3.3V to 5V, fix LFO biasing, LPF, JFET bias trim pots.
2019-01-31 add quantization switches
2019-01-31 add envelope repeat switches
2019-02-01 simulate bias voltage buffer. Previous op amp approach couldn't go close enough to the rails.
2019-02-01 update schematics with NPN bias buffer
2019-02-01 add delay mix control. Currently 50/50 is max possible wet/dry, but this might change.
2019-02-01 fix quantization range by pre-computing the conversion from note frequencies to their corresponding ADC values.
2019-02-01 quantize all 4 oscillators for now
2019-02-05 change delay summing to balance control to allow 0-100% wet signal, rather than 0-50%.
2019-02-05 change emitter resistors on JFET bias buffers
2019-02-07 begin PCB v2 layout. fix ref designators, associate footprints on new components, create new PCB file, import components.
2019-02-07 add separate Kicad project for control board. There will now be a separate board for all potentiometers and switches with no other components. Also add connectors between boards.
2019-02-07 add control board connects to main synth schematic
2019-02-08 connect control board to main synth schem pages
2019-02-08 add connectors for capsense buttons and LFO shape switch
2019-02-09 fix missing connectors in main synth project
2019-02-09 create initial panel artwork design and update the BOM with some mechanical items.
2019-02-09 reduce drill size on panel artwork and add intermod switch
2019-02-09 add key up/down switches to panel layout
2019-02-09 move up center effects box on panel
2019-02-11 add volume pots to control board
2019-02-11 place MCU footprints
2019-02-11 place delay and output mixer footprints
2019-02-11 place LFO footprints
2019-02-12 place filter footprints
2019-02-12 add LFO mod pots to control board and fix pot placement
2019-02-12 route traces to bypass caps on MCU. control board and connectors are WIP.
2019-02-13 route connectors on control board. Will add additional set of connectors for filter knobs to simplify routing.
2019-02-13 add copper pour GND layer to control board
2019-02-13 add frequency and LFO connectors to control board
2019-02-13 match relative connector placement between two boards
2019-02-13 route filter connectors to op amp
2019-02-13 route envelope op amps
2019-02-13 route JFET biasing network
2019-02-13 fix LFO connector schem
2019-02-13 route LFO
2019-02-13 place delay footprints
2019-02-13 route majority of delay components
2019-02-14 finish routing connectors and start routing +15V
2019-02-14 PCBv2 release candidate. Passes DRC.
2019-02-20 very buggy initial digital delay prototype
2019-02-20 improve delay buffer indexing.
2019-02-20 add mounting holes to control board PCB
2019-02-21 update BOM with new switch and knob prices from Aliexpress
2019-02-21 update control board with new pot placement from panel update
2019-02-21 tentative edge cut on control board update
2019-02-22 move main synth board so that connector dimensions match between boards.
2019-02-22 fix remaining connector placement. Routing still WIP
2019-02-23 redo connector routing with 2-row connectors
2019-02-24 mostly done rerouting main board. Still some ground returns to take care of.
2019-02-25 add quantization again, fix connectors again, add mounting holes to main board
2019-02-25 redo second connector on main board
2019-02-26 reroute connector board with 2-row connectors. Hold switch placement is temporary. Need to find room for this.
2019-02-26 increase control board size to accomodate hold switch placement. Hopefully, this is the final panel design.
2019-02-26 fix filter pots. Dual ganged pot footprint was incorrect.
2019-02-26 add end stop resistors and reservoir caps to potentiometers.
2019-02-26 fix some missing traces on main board
2019-02-26 new release candidate. Passes DRC.
2019-02-26 fix remaining switch footprints
2019-02-28 add version labels to PCB silkscreen
2019-02-28 arrange reference designators on main board
2019-02-28 add missing RC feedback network for MCU delay. Probably won't end up using this, but it's there if I need it.
2019-02-28 some schematic changes missing from previous commit. (didn't save)
2019-03-01 update BOM for v2 sample.
2019-03-06 update back panel with current rating
2019-03-11 fix frequency, PWM ADC inputs, and quantization digital inputs
2019-03-12 add USB MIDI enumeration code. This is largely copied from the Cypress code examples. Enumeration works and the device shows up in Reaper, but I haven't tested sending MIDI messages yet.
2019-03-12 move USB MIDI code into separate files
2019-03-12 move USB enumeration into separate function
2019-03-13 consolidate envelope and ADC update code into functions.
2019-03-13 fix envelope PWM generation by changing the envelope struct to store a pointer to the PWM value. Now the envelope PWM value ramps up correctly, although there is still an issue with reading the envel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
2019-03-15 fix envelope spead ADC input mux.
2019-03-19 add some reference materials on JFET VCAs
2019-03-19 split top design into different pages
2019-03-20 clean up and documentation
2019-03-20 simplify code to set ADC values by making oscillator structs.
2019-03-20 remove old freq and pulse_width variables which are no longer used.
2019-03-21 dispatch MIDI notes to first available oscillator. Not quite working yet, but this is the correct structure.
2019-03-21 make some changes to button logic. It was incorrectly checking hold and repeat switches.
2019-03-21 MIDI sequencing works. Can send notes from Reaper and my synth plays them. Only testing on Osc_0 right now.
2019-03-21 two voice polyphony is working.
2019-03-21 four voice polyphony is working.
2019-03-22 fix incorrect hold switch GPIO. I'll need to go through and rename everything because the numbers don't correspond to the channels. The pinout is correct, but the naming is wrong.
2019-03-22 note off MIDI messages check frequencies and only turn off the correct notes.
2019-03-27 fix net naming error on control board
2019-03-28 fix backward filter potentiometers
2019-03-29 increase delay time pot value. End stop resistor is still fine.
2019-04-01 change delay fb control to log taper.
